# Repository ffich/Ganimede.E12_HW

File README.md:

# Ganimede.E12_HW
Public repo for ganimede.E12 hardware project.

# What Ganimede is?
The Ganimede is a family of fancy development boards based on ESP8266 and ESP32 SoC from EspressIf.
The idea behind Ganimede is that I started to be bored of soldering, breadboarding and, more in general, to have messy connection between my development board and the sensor and actuators I needed for my experiments and projects.
Additionally, after the experience with Mercury System, I decided to not to do again such a crazy thing in which I had to make all the HW and SW, as it required literally hundreds of days and it's not sustainable (and even if it would be, Anna would probably kill me). Moreover, I do love C, but I understand that this is not the same for everybody and is also a bit limiting, so welcome to Python and Javascript. Last but not least, I wanted to have something really cheap, that can be used by me, friends and (possibly) others.
So, in the end, Ganimede is a development board with the following characteristics:

1. It's based on ESP SoC with integrated peripherals like WiFi, BT and USB.
2. It carries some sockets/connectors that allow to use well known standards (Mikroe MikroBUS, SeedStudio grove, others), so no more messy connections with sensor/actuators around your desk.
3. Can be programmed in C/C++, Python and Javascript.
4. It's really cheap.
5. It's open hardware, I will share schematics and design files.
6. It's really simple to use.

# Ganimede.E12
Ganimede.E12 is the version based on ESP8266 (more specifically on the ESP-12 module by AI-Thinker). The hardware details of Ganimede.E12 are resumed in the picture below:

## Main characteristics of Ganimede.E12:
- USB connection for communication, Power and Flashing
- WiFi
- 11x GPIO
- 2x User LEDs
- 2x User buttons
- 1x MikroBUS Socket
- 1x Grove Connector
- 1x Neopixel/1-wire Connector
- 2x OLED Connectors

If you want more information you can have a look at the [Ganimede.E12 Datasheet](https://2492ae4f-d323-49c0-bc1e-8d5936f83a9d.usrfiles.com/ugd/2492ae_11933c1aee514b55b51fd540d7772119.pdf) and to the [Ganimede.E12 Product Page](https://frafich.wixsite.com/jupitersystem/product-page/ganimede-e12).

# Ganimede.E12 HW project
This repo contains the full HW project of Ganimede.E12, with the traditional file structure I use on my HW projects, and more specifically:
- 10_PCB: contains the Kicad 6.x project of the board. The **jlcpcb** folder contains all the files needed for making the board using JLCPCB service.
- 20_SCH: contains the board's schematic in PDF.
- 30_BOMS: contains a fancy iBOM (made using the iBOM plugin by [https://github.com/openscopeproject](https://github.com/openscopeproject)) and a more traditional BOM file.
- 40_GERBERS: contains Gerber and Centronic files. These files allow you to make your own board by yourself or using traditional PCB/Manufacturing services (e.g. PcbWay).
- 50_3D: contains a 3D view of the board.
- 60_LIB: contains some additional 3D files (mostly step) I needed for making the board's 3D.

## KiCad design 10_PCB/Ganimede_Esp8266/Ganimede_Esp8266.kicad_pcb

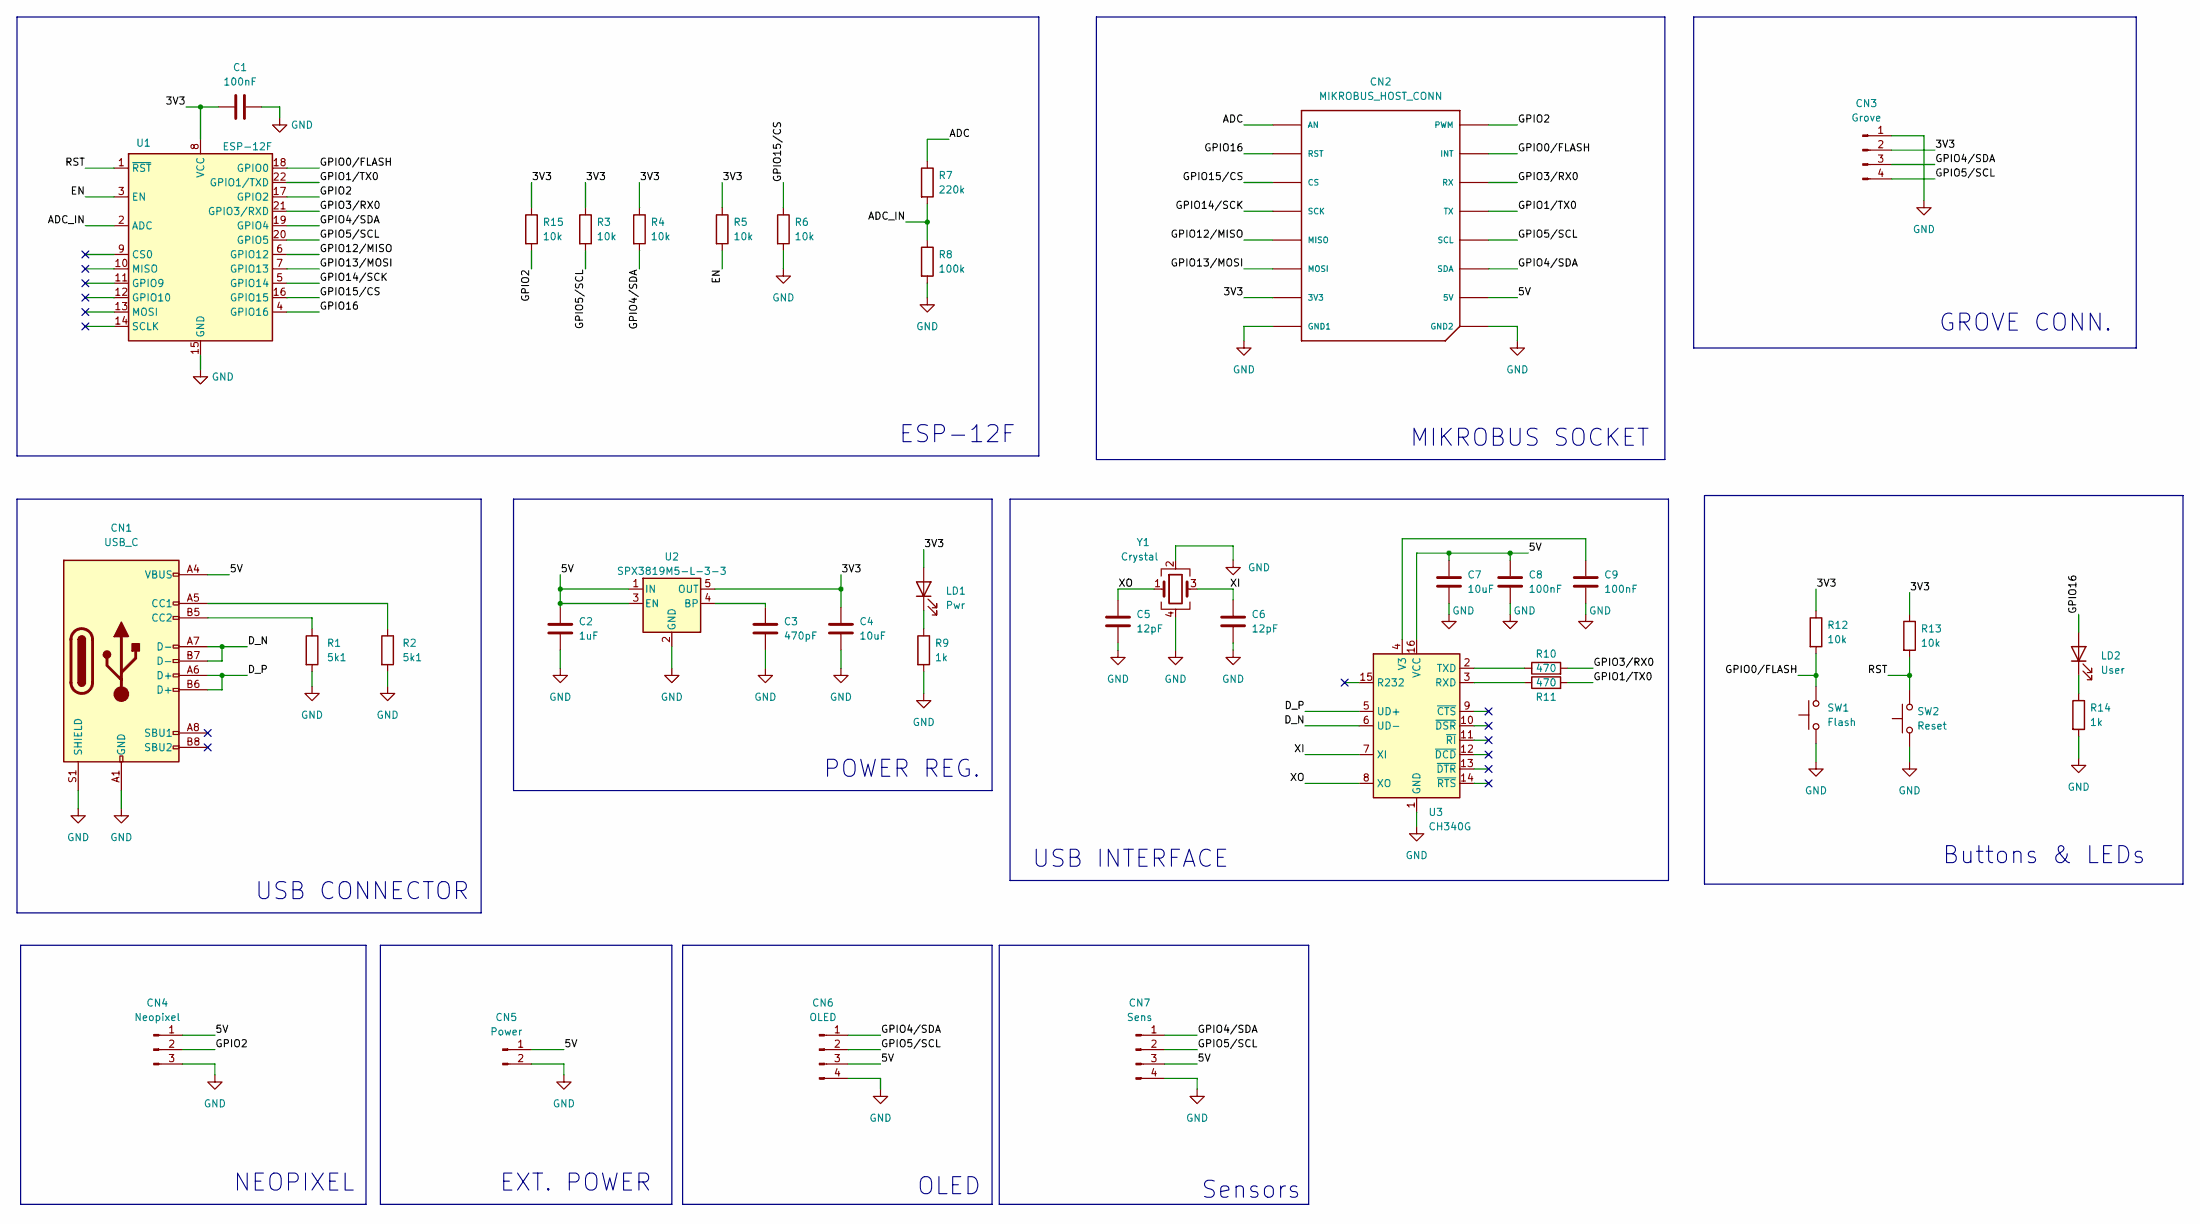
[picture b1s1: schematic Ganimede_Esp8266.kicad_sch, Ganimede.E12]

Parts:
C1, C8, C9: 100nF; C_0402_1005Metric; LCSC C1525
C2: 1uF; C_0402_1005Metric; LCSC C52923
C3: 470pF; C_0402_1005Metric; LCSC C1537
C4, C7: 10uF; C_0402_1005Metric; LCSC C15525
C5, C6: 12pF; C_0402_1005Metric; LCSC C1547
CN1: USB_C; USB_C_Receptacle_HRO_TYPE-C-31-M-12; LCSC C165948
CN2: MIKROBUS_HOST_CONN
CN3: Grove; JST_PH_S4B-PH-K_1x04_P2.00mm_Horizontal
CN4: Neopixel; PinHeader_1x03_P2.54mm_Vertical
CN5: Power; PinHeader_1x02_P2.54mm_Vertical
CN6: OLED; PinHeader_1x04_P2.54mm_Vertical
CN7: Sens; PinHeader_1x04_P2.54mm_Vertical
LD1: Pwr; LED_0603_1608Metric; LCSC C2286
LD2: User; LED_0603_1608Metric; LCSC C2288
R1, R2: 5k1; R_0402_1005Metric; LCSC C25905
R3, R4, R5, R6, R12, R13, R15: 10k; R_0402_1005Metric; LCSC C25744
R7: 220k; R_0402_1005Metric; LCSC C25767
R8: 100k; R_0402_1005Metric; LCSC C25741
R9, R14: 1k; R_0402_1005Metric; LCSC C11702
R10, R11: 470; R_0402_1005Metric; LCSC C25117
SW1: Flash; SW_Push_1P1T_NO_6x6mm_H9.5mm; LCSC C127509
SW2: Reset; SW_Push_1P1T_NO_6x6mm_H9.5mm; LCSC C127509
U1: ESP-12F; ESP-12E; LCSC C82891
U2: SPX3819M5-L-3-3; SOT-23-5; LCSC C9055
U3: CH340G; SOIC-16_3.9x9.9mm_P1.27mm; LCSC C14267
Y1: Crystal; Crystal_SMD_3225-4Pin_3.2x2.5mm; LCSC C9002

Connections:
/3V3: C1.1, C4.1, CN2.P7 (3V3), CN3.2, LD1.2 (A), R3.1, R4.1, R5.1, R12.1, R13.1, R15.1, U1.8 (VCC), U2.5 (OUT)
/5V: C2.1, C7.1, C8.1, CN1.A4 (VBUS), CN1.A9 (VBUS), CN1.B4 (VBUS), CN1.B9 (VBUS), CN2.P10 (5V), CN4.1, CN5.1, CN6.3, CN7.3, U2.1 (IN), U2.3 (EN), U3.16 (VCC)
/ADC: CN2.P1 (AN), R7.1
/ADC_IN: R7.2, R8.1, U1.2 (ADC)
/D_N: CN1.A7 (D-), CN1.B7 (D-), U3.6 (UD-)
/D_P: CN1.A6 (D+), CN1.B6 (D+), U3.5 (UD+)
/EN: R5.2, U1.3 (EN)
/GPIO0/FLASH: CN2.P15 (INT), R12.2, SW1.2, U1.18 (GPIO0)
/GPIO1/TX0: CN2.P13 (TX), R11.2, U1.22 (GPIO1/TXD)
/GPIO2: CN2.P16 (PWM), CN4.2, R15.2, U1.17 (GPIO2)
/GPIO3/RX0: CN2.P14 (RX), R10.2, U1.21 (GPIO3/RXD)
/GPIO4/SDA: CN2.P11 (SDA), CN3.3, CN6.1, CN7.1, R4.2, U1.19 (GPIO4)
/GPIO5/SCL: CN2.P12 (SCL), CN3.4, CN6.2, CN7.2, R3.2, U1.20 (GPIO5)
/GPIO12/MISO: CN2.P5 (MISO), U1.6 (GPIO12)
/GPIO13/MOSI: CN2.P6 (MOSI), U1.7 (GPIO13)
/GPIO14/SCK: CN2.P4 (SCK), U1.5 (GPIO14)
/GPIO15/CS: CN2.P3 (CS), R6.1, U1.16 (GPIO15)
/GPIO16: CN2.P2 (RST), LD2.2 (A), U1.4 (GPIO16)
/RST: R13.2, SW2.2, U1.1 (~RST)
/XI: C6.1, U3.7 (XI), Y1.3
/XO: C5.1, U3.8 (XO), Y1.1
GND: C1.2, C2.2, C3.2, C4.2, C5.2, C6.2, C7.2, C8.2, C9.2, CN1.A1 (GND), CN1.A12 (GND), CN1.B1 (GND), CN1.B12 (GND), CN1.S1 (SHIELD), CN2.P8 (GND1), CN2.P9 (GND2), CN3.1, CN4.3, CN5.2, CN6.4, CN7.4, R1.2, R2.2, R6.2, R8.2, R9.2, R14.2, SW1.1, SW2.1, U1.15 (GND), U2.2 (GND), U3.1 (GND), Y1.2, Y1.4
unnamed: C3.1, U2.4 (BP)
unnamed: C9.1, U3.4 (V3)
unnamed: CN1.A5 (CC1), R2.1
unnamed: CN1.B5 (CC2), R1.1
unnamed: LD1.1 (K), R9.1
unnamed: LD2.1 (K), R14.1
unnamed: R10.1, U3.2 (TXD)
unnamed: R11.1, U3.3 (RXD)

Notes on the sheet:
GROVE CONN.
ESP-12F
Buttons & LEDs
POWER REG.
OLED
USB CONNECTOR
EXT. POWER
Sensors
NEOPIXEL
MIKROBUS SOCKET
USB INTERFACE

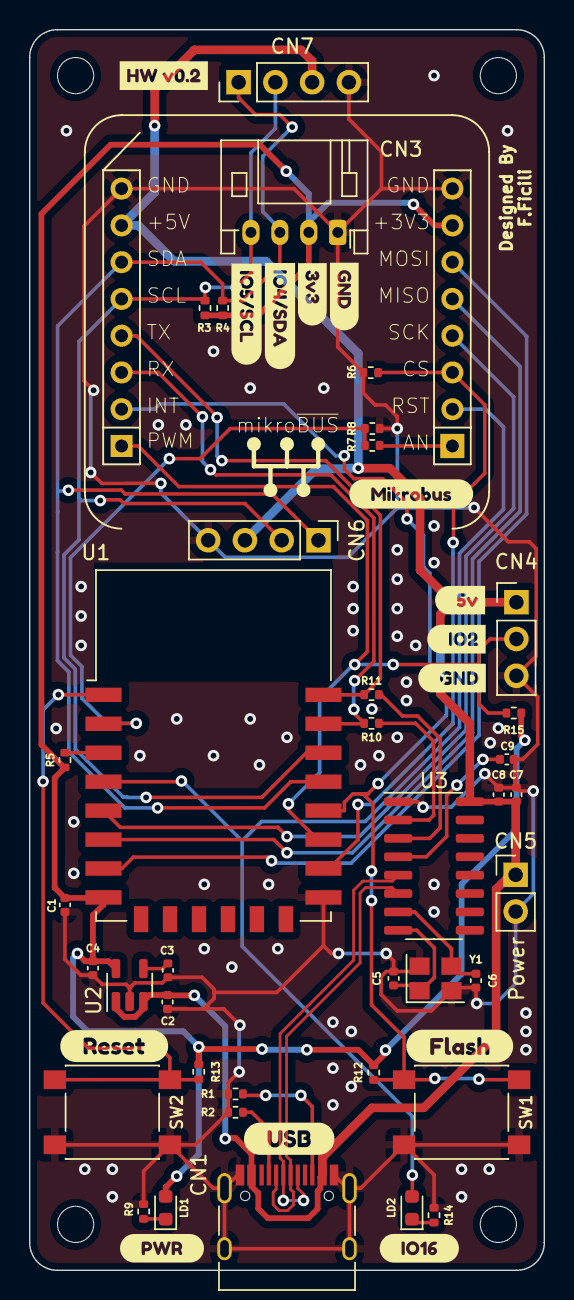
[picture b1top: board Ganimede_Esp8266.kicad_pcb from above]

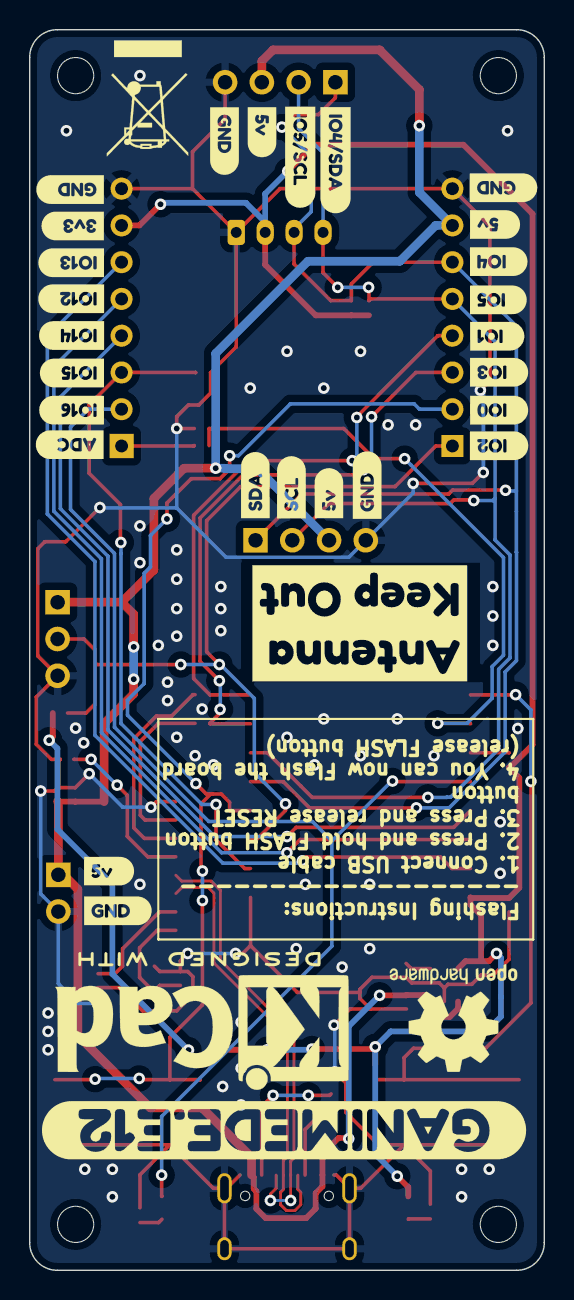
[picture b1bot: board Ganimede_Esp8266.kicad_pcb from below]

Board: 2 copper layers, 35.6 x 85.7 mm, 81 parts (28 on the bottom side), 30 nets.

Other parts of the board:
kibuzzard-62924A8F: G***; kibuzzard-62924A8F
kibuzzard-62924A99: G***; kibuzzard-62924A99
kibuzzard-62925DA5: G***; kibuzzard-62925DA5
kibuzzard-62925DB7: G***; kibuzzard-62925DB7
kibuzzard-627569F9: G***; kibuzzard-627569F9
kibuzzard-629249FD: G***; kibuzzard-629249FD
kibuzzard-629255AA: G***; kibuzzard-629255AA
kibuzzard-629255B3: G***; kibuzzard-629255B3
kibuzzard-629255BF: G***; kibuzzard-629255BF
kibuzzard-629255D4: G***; kibuzzard-629255D4
kibuzzard-629255EA: G***; kibuzzard-629255EA
kibuzzard-629255F7: G***; kibuzzard-629255F7
kibuzzard-629256A8: G***; kibuzzard-629256A8
kibuzzard-629258C9, kibuzzard-629258C9#2: G***; kibuzzard-629258C9
kibuzzard-629258DB, kibuzzard-629258DB#2: G***; kibuzzard-629258DB
kibuzzard-629263D2, kibuzzard-629263D2#2: G***; kibuzzard-629263D2
kibuzzard-629263EA: G***; kibuzzard-629263EA
kibuzzard-6275539F: G***; kibuzzard-6275539F
kibuzzard-6292541E: G***; kibuzzard-6292541E
kibuzzard-6292551A: G***; kibuzzard-6292551A
kibuzzard-6292567C: G***; kibuzzard-6292567C
kibuzzard-6292569E: G***; kibuzzard-6292569E
kibuzzard-6292591F, kibuzzard-6292591F#2: G***; kibuzzard-6292591F
kibuzzard-62755375: G***; kibuzzard-62755375
kibuzzard-62755551: G***; kibuzzard-62755551
kibuzzard-62769624: G***; kibuzzard-62769624
kibuzzard-62925408: G***; kibuzzard-62925408
kibuzzard-62925415: G***; kibuzzard-62925415
kibuzzard-62925591: G***; kibuzzard-62925591
kibuzzard-62925659: G***; kibuzzard-62925659
kibuzzard-62925667: G***; kibuzzard-62925667
kibuzzard-62925672: G***; kibuzzard-62925672
kibuzzard-62925687: G***; kibuzzard-62925687
kibuzzard-62925693: G***; kibuzzard-62925693
kibuzzard-62925732: G***; kibuzzard-62925732
kibuzzard-62925915: G***; kibuzzard-62925915
kibuzzard-62926402: G***; kibuzzard-62926402
kibuzzard-62926416: G***; kibuzzard-62926416

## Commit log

2022-08-04 First commit of Ganimede.E12 HW project.
